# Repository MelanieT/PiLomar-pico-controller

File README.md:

# Pilomar Pico firmware

## Firmware for driving two standard stepper drivers

You can use the board files in hardware/ to have the board fabbed, or you can use a stock pico and wire up the stepper drivers according to the schematic.

The pico will appear as a USB network device and two serial ports, the first of which is the console, which is also available on a JST-SM connector on the board.

It serves a REST API as described in the PilomarAPI.yaml file, which is maintained in the jPiLomar project.

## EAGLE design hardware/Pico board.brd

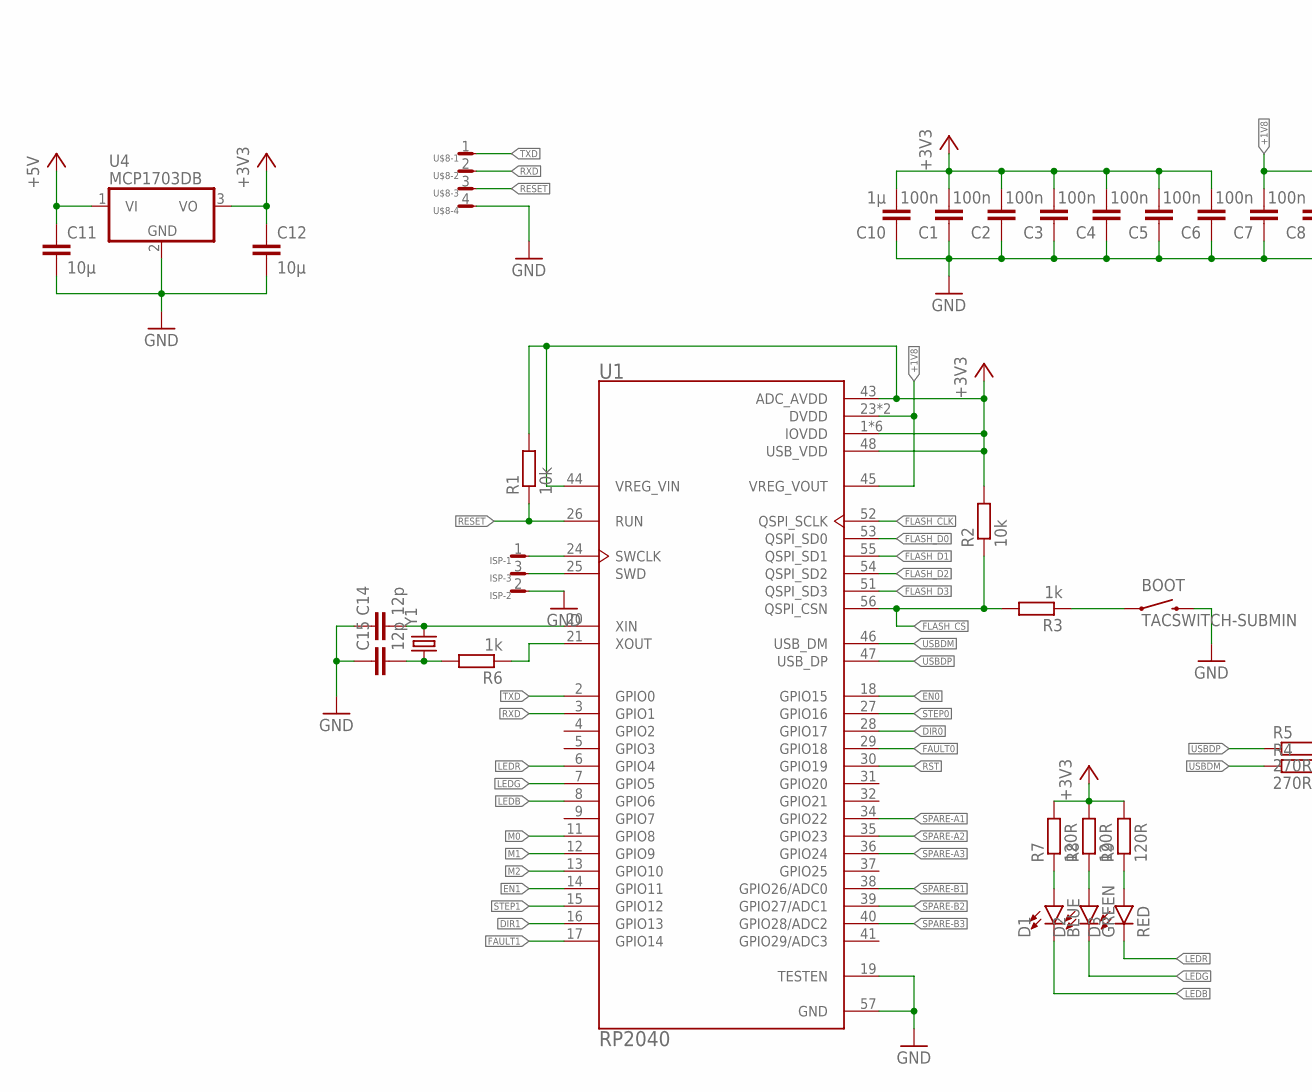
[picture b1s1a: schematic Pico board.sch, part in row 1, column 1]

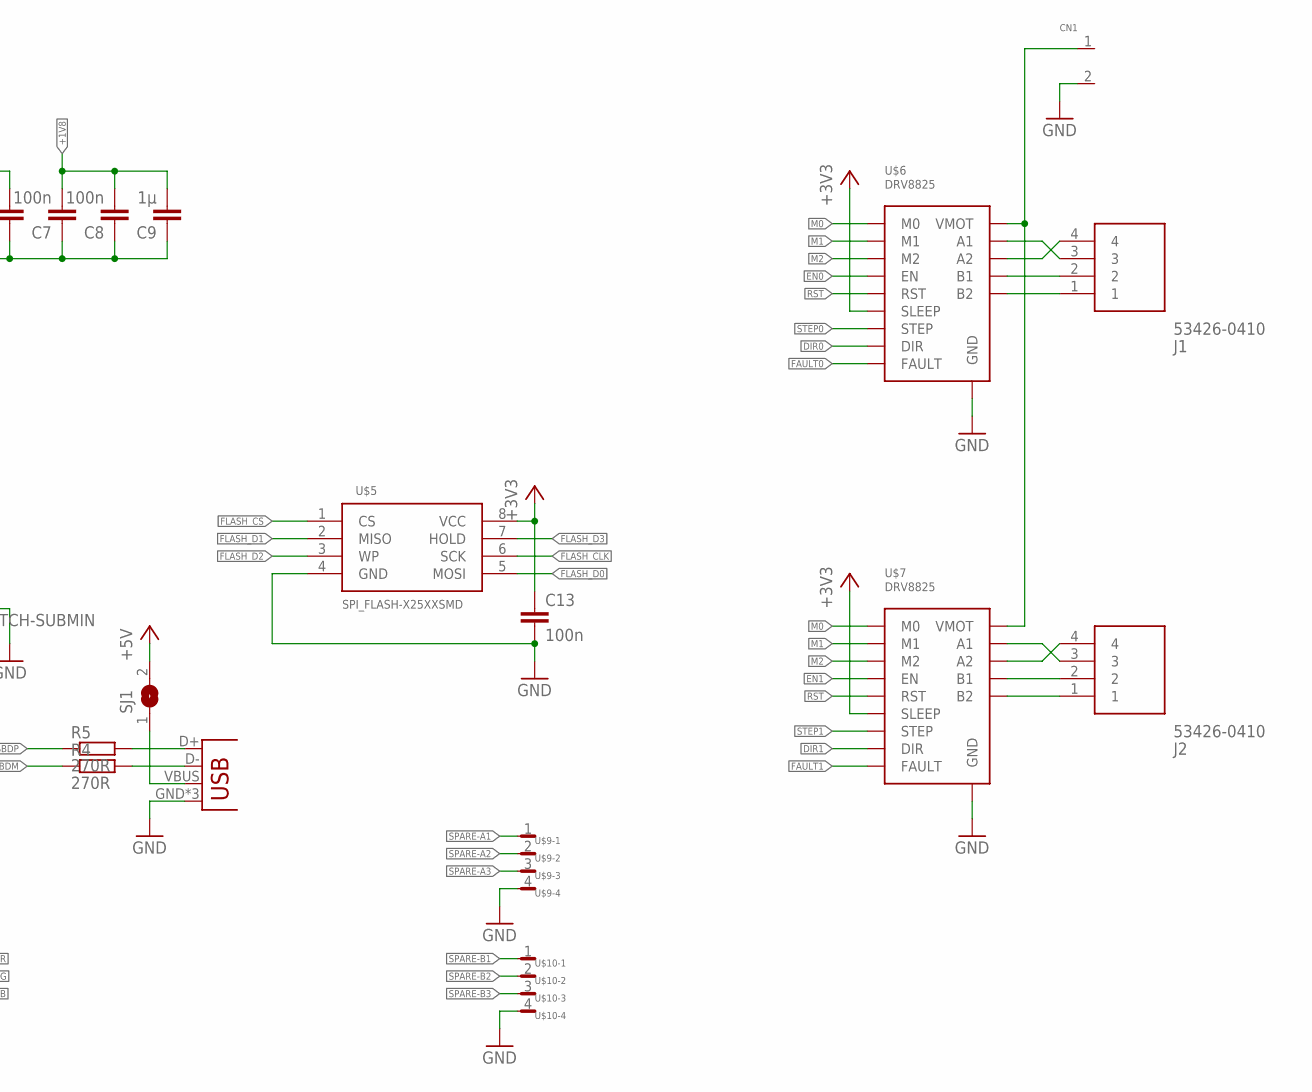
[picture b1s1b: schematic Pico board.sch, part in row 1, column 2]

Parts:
BOOT: TACSWITCH-SUBMIN; TACSWITCH_SUBMIN
C1, C2, C3, C4, C5, C6, C7, C8, C13: 100n; C0402K
C9, C10: 1µ; C0603K
C11, C12: 10µ; C1206K
C14, C15: 12p; C0402K
CN1: 2PIN_SCREW_TRM; CONN2P
D1: BLUE; LED-0603
D2: GREEN; LED-0603
D3: RED; LED-0603
ISP: SM03B-SRSS-TB
J1, J2: 53426-0410; SHDRRA4W55P0X250_1X4_1240X1150
JP1: USB-MICROB
R1, R2: 10k; R0402
R3, R6: 1k; R0402
R4, R5: 270R; R0402
R7, R8, R9: 120R; R0402
SJ1: SJ
U1: RP2040; QFN40P700X700X90-57N
U4: MCP1703DB; SOT223
U$5: SPI_FLASH-X25XXSMD; SO08
U$6, U$7: DRV8825; POLOLU
U$8, U$9, U$10: SM04B-SRSS-TB
Y1: CRYSTAL5X3; CRYSTAL-SMD-5X3

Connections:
+1V8: C7.2, C8.2, C9.2, U1.23 (DVDD), U1.45 (VREG_VOUT), U1.50 (DVDD)
+3V3: C1.2, C2.2, C3.2, C4.2, C5.2, C6.2, C10.2, C12.1, C13.1, R1.2, R2.2, R7.2, R8.2, R9.2, U1.1 (IOVDD), U1.10 (IOVDD), U1.22 (IOVDD), U1.33 (IOVDD), U1.42 (IOVDD), U1.43 (ADC_AVDD), U1.44 (VREG_VIN), U1.48 (USB_VDD), U1.49 (IOVDD), U4.3 (VO), U$5.8 (VCC), U$6.SLEEP, U$7.SLEEP
+5V: C11.1, SJ1.2, U4.1 (VI)
DIR0: U1.28 (GPIO17), U$6.DIR
DIR1: U1.16 (GPIO13), U$7.DIR
EN0: U1.18 (GPIO15), U$6.ENABLE (EN)
EN1: U1.14 (GPIO11), U$7.ENABLE (EN)
FAULT0: U1.29 (GPIO18), U$6.FAULT
FAULT1: U1.17 (GPIO14), U$7.FAULT
FLASH_CLK: U1.52 (QSPI_SCLK), U$5.6 (SCK)
FLASH_CS: R2.1, R3.2, U1.56 (QSPI_CSN), U$5.1 (CS)
FLASH_D0: U1.53 (QSPI_SD0), U$5.5 (MOSI)
FLASH_D1: U1.55 (QSPI_SD1), U$5.2 (MISO)
FLASH_D2: U1.54 (QSPI_SD2), U$5.3 (WP)
FLASH_D3: U1.51 (QSPI_SD3), U$5.7 (HOLD)
GND: BOOT.-2 (2), C1.1, C2.1, C3.1, C4.1, C5.1, C6.1, C7.1, C8.1, C9.1, C10.1, C11.2, C12.2, C13.2, C14.1, C15.1, CN1.2, ISP.2, JP1.GND, JP1.MT1 (GND), JP1.MT2 (GND), U1.19 (TESTEN), U1.57 (GND), U4.2 (GND), U$5.4 (GND), U$6.GND@1 (GND), U$6.GND@2 (GND), U$7.GND@1 (GND), U$7.GND@2 (GND), U$8.4, U$9.4, U$10.4
LEDB: D1.C, U1.8 (GPIO6)
LEDG: D2.C, U1.7 (GPIO5)
LEDR: D3.C, U1.6 (GPIO4)
M0: U1.11 (GPIO8), U$6.M0, U$7.M0
M1: U1.12 (GPIO9), U$6.M1, U$7.M1
M2: U1.13 (GPIO10), U$6.M2, U$7.M2
unnamed: J1.3, U$6.A1
unnamed: JP1.D+, R5.2
unnamed: JP1.D-, R4.2
unnamed: J1.4, U$6.A2
unnamed: BOOT.-1 (1), R3.1
unnamed: J2.2, U$7.B1
unnamed: J2.1, U$7.B2
unnamed: J2.3, U$7.A1
unnamed: J2.4, U$7.A2
unnamed: JP1.VBUS, SJ1.1
unnamed: ISP.1, U1.24 (SWCLK)
unnamed: ISP.3, U1.25 (SWD)
unnamed: C15.2, R6.2, Y1.1
unnamed: R6.1, U1.21 (XOUT)
unnamed: C14.2, U1.20 (XIN), Y1.3 (2)
unnamed: J1.2, U$6.B1
unnamed: J1.1, U$6.B2
unnamed: D1.A, R7.1
unnamed: D2.A, R8.1
unnamed: CN1.1, U$6.VMOT, U$7.VMOT
unnamed: D3.A, R9.1
RESET: R1.1, U1.26 (RUN), U$8.3
RST: U1.30 (GPIO19), U$6.RESET (RST), U$7.RESET (RST)
RXD: U1.3 (GPIO1), U$8.2
SPARE-A1: U1.34 (GPIO22), U$9.1
SPARE-A2: U1.35 (GPIO23), U$9.2
SPARE-A3: U1.36 (GPIO24), U$9.3
SPARE-B1: U1.38 (GPIO26/ADC0), U$10.1
SPARE-B2: U1.39 (GPIO27/ADC1), U$10.2
SPARE-B3: U1.40 (GPIO28/ADC2), U$10.3
STEP0: U1.27 (GPIO16), U$6.STEP
STEP1: U1.15 (GPIO12), U$7.STEP
TXD: U1.2 (GPIO0), U$8.1
USBDM: R4.1, U1.46 (USB_DM)
USBDP: R5.1, U1.47 (USB_DP)

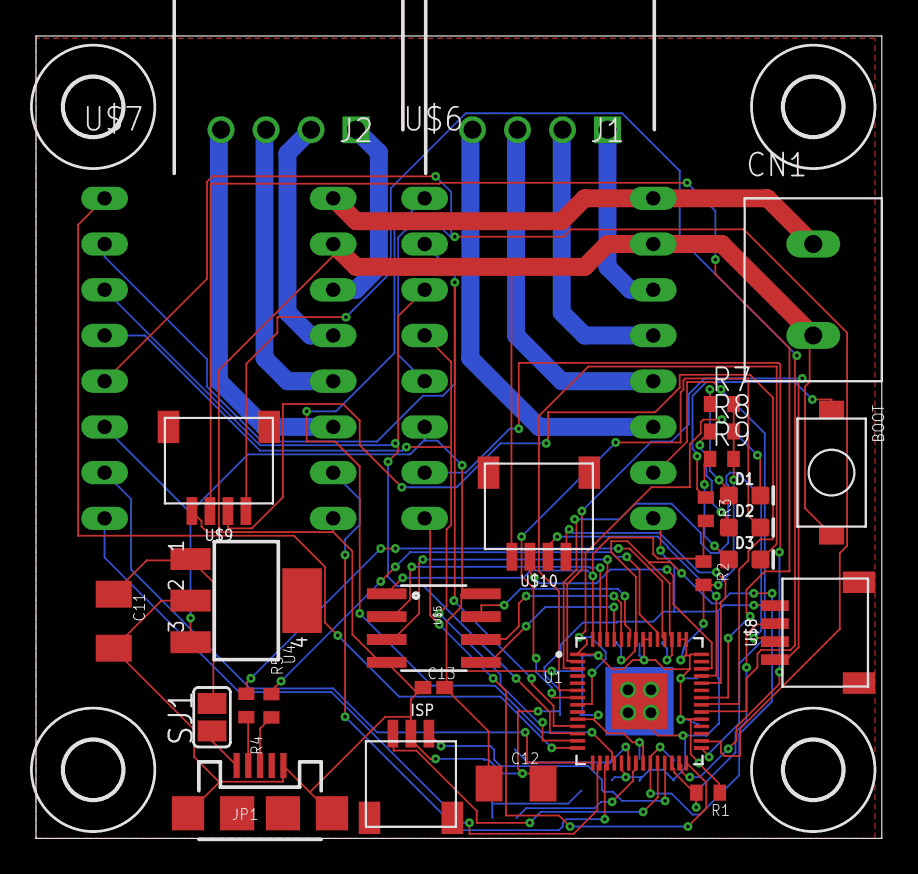
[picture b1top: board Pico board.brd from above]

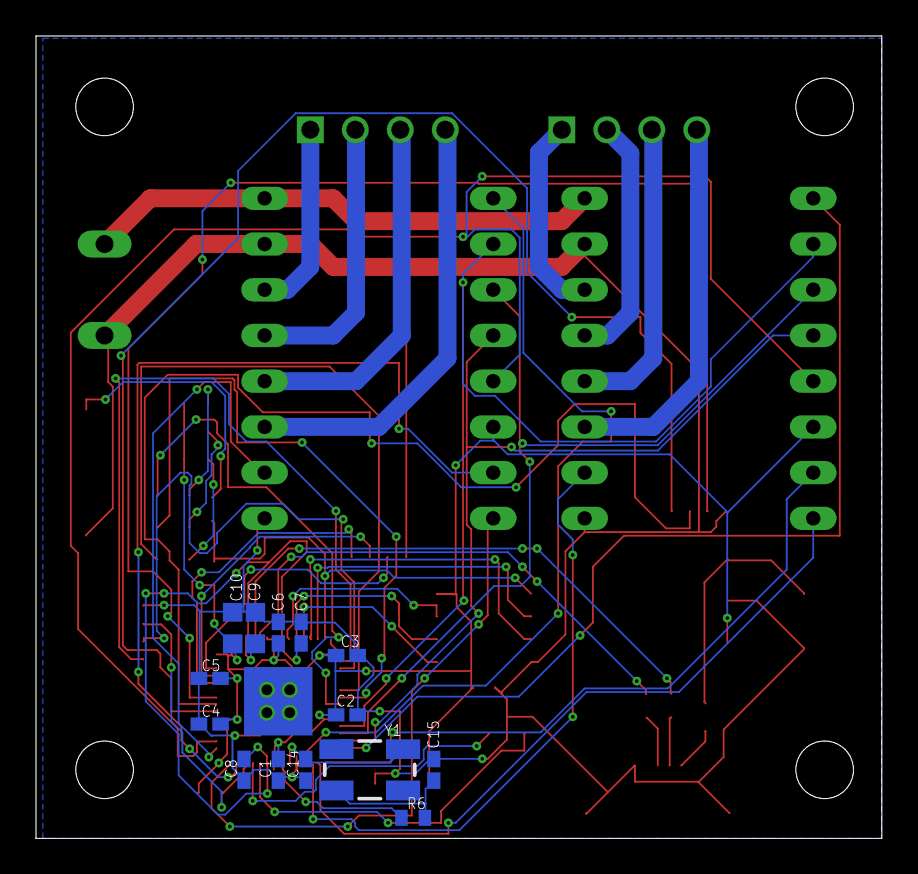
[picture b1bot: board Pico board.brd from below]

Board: 2 copper layers, 47.0 x 44.6 mm, 47 parts (14 on the bottom side), 57 nets.

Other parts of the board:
U$1, U$2, U$3, U$4: 3,2

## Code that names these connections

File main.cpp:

// SPDX-FileCopyrightText: 2024 Melanie Thielker & Leonie Gaertner
// SPDX-License-Identifier: BSD-3-Clause

#include <cstdio>
#include <pico/time.h>
#include <hardware/gpio.h>
#include <vector>
#include <pico/stdlib.h>
#include <hardware/flash.h>
#include "pico/stdio.h"
#include "Motor.h"
#include "tusb.h"
#include "tusb_lwip_glue.h"
#include "webserver/WebServer-lwip.h"
#include "webserver/ApiServer.h"
#include "UrlMapper.h"
#include "nlohmann/json.hpp"

#define MODE_DOOR 0
#define MODE_CAMERA 1
#define MODE MODE_CAMERA

#define LED_BLUE  4
#define LED_GREEN 5
#define LED_RED   6
#define STEP_M0   8
#define STEP_M1   9
#define STEP_M2   10
#define RST       19
#define EN0       15
#define STEP0     16
#define DIR0      17
#define VCC0      18
#define EN1       11
#define STEP1     12
#define DIR1      13
#define VCC1      14

#define SPARE_A1  22
#define SPARE_A2  23
#define SPARE_A3  24

#define SPARE_B1  26
#define SPARE_B2  27
#define SPARE_B3  28

#define AZIMUTH_MAX_SPEED 8000
#define AZIMUTH_STEPS_PER_REVOLUTION 384000
#define AZIMUTH_MAX_STEPS 384000 //373334

#define ELEVATION_MAX_SPEED 8000
#define ELEVATION_STEPS_PER_REVOLUTION 384000
#define ELEVATION_MAX_STEPS 120000
#define ELEVATION_ZERO_POINT 22500

#define DOOR_MAX_STEPS 2125
#define DOOR_MAX_SPEED 400

using namespace nlohmann;

uint8_t macaddr[6];

uint8_t tud_network_mac_address[6];

Motor *stepper0;
Motor *stepper1;

WebServerLwip webserver;

class PilomarApi
{
public:
    static void Init()
    {
        UrlMapper::AddMapping("GET", "/info", &info);
        UrlMapper::AddMapping("POST", "/move", &move);
    }
private:
#if MODE == MODE_DOOR
    static void move(const HttpRequest& request, HttpResponse& response)
    {
        auto payload = json::parse(request.body(), nullptr, false);
        if (payload.is_discarded())
        {
            response.setStatusCode(HttpStatus::Code::BadRequest);
            return;
        }

        if (stepper0->isRunning() || stepper1->isRunning())
        {
            response.setStatusCode(HttpStatus::Code::PreconditionFailed);
            return;
        }

        auto mode = payload.value<std::string>("mode", "move");

        if (mode == "move")
        {
            int position = payload.value("position", -1);
            int speed = payload.value("speed", DOOR_MAX_SPEED);

            if (position < 0 || position > DOOR_MAX_STEPS || speed < 10 || speed > DOOR_MAX_SPEED)
            {
                response.setStatusCode(HttpStatus::Code::BadRequest);
                return;
            }
            stepper0->runToTarget(speed, position);
            stepper1->runToTarget(speed, position);
        }
        else if (mode == "learn")
        {
            stepper0->setCurrentPosition(DOOR_MAX_STEPS);
            stepper1->setCurrentPosition(DOOR_MAX_STEPS);
            stepper0->runToTarget(DOOR_MAX_SPEED, 0);
            stepper1->runToTarget(DOOR_MAX_SPEED, 0);
        }
        else
        {
            response.setStatusCode(HttpStatus::Code::BadRequest);
            return;
        }

        response.setBody(
                json{
                    {"result", "ok"}
                }.dump()
            );
    }
#elif MODE == MODE_CAMERA
#pragma clang diagnostic push
#pragma ide diagnostic ignored "bugprone-branch-clone"
    static void move(const HttpRequest& request, HttpResponse& response)
    {
        auto payload = json::parse(request.body(), nullptr, false);
        if (payload.is_discarded())
        {
            response.setStatusCode(HttpStatus::Code::BadRequest);
            return;
        }

        auto motor = payload.value<std::string>("motor", "");
        Motor *m = nullptr;
        if (motor == "azimuth")
            m = stepper1;
        else if (motor == "elevation")
            m = stepper0;

        if (!m)
        {
            response.setStatusCode(HttpStatus::Code::BadRequest);
            return;
        }

//        if (m->isRunning())
//        {
//            response.setStatusCode(HttpStatus::Code::PreconditionFailed);
//            return;
//        }

        int maxSpeed = motor == "elevation" ? ELEVATION_MAX_SPEED : AZIMUTH_MAX_SPEED;
        int maxSteps = motor == "elevation" ? ELEVATION_MAX_STEPS : AZIMUTH_MAX_STEPS;

        int position = payload.value("position", -1);
        auto speed = payload.value<double>("speed", (double)maxSpeed);

        if (position < 0 || position > maxSteps || speed < 0.0001 || speed > maxSpeed)
        {
            response.setStatusCode(HttpStatus::Code::BadRequest);
            return;
        }

        m->runToTarget(speed, position);

        response.setBody(
            json{
                {"result", "ok"}
            }.dump()
        );
    }
#pragma clang diagnostic pop
#endif
    static void info(const HttpRequest& request, HttpResponse& response)
    {
        response.setBody(
            json{
#if MODE == MODE_DOOR
                {"type", "door"},
                {"max_steps", DOOR_MAX_STEPS},
                {"max_speed", DOOR_MAX_SPEED},
                {"position_left", stepper0->getCurrentPosition()},
                {"position_right", stepper1->getCurrentPosition()},
                {"closed_position", 0},
                {"open_position", DOOR_MAX_STEPS}
#elif MODE == MODE_CAMERA
                {"type", "camera"},
                {"azimuth", stepper1->getCurrentPosition()},
                {"elevation", stepper0->getCurrentPosition()},
                {"max_elevation", ELEVATION_MAX_STEPS},
                {"max_azimuth", AZIMUTH_MAX_STEPS},
                {"max_speed_azimuth", AZIMUTH_MAX_SPEED},
                {"max_speed_elevation", ELEVATION_MAX_SPEED}
#endif
            }.dump()
        );
    }
};

void usbd_serial_init(void)
{
    uint8_t id[8];

    flash_get_unique_id(id);

    tud_network_mac_address[0] = 0xb8;
    tud_network_mac_address[1] = 0x27;
    tud_network_mac_address[2] = 0xeb;
    tud_network_mac_address[3] = id[5];
    tud_network_mac_address[4] = id[6];
    tud_network_mac_address[5] = id[7];
}

#pragma clang diagnostic push
#pragma ide diagnostic ignored "EndlessLoop"
int main()
{
    usbd_serial_init();
    tusb_init();
    stdio_init_all();

    init_lwip();

    wait_for_netif_is_up();

    dhcpd_init();

    webserver.Init();
    PilomarApi::Init();

    std::vector<uint> gpios_out = {4, 5, 6, 8, 9, 10, 11, 12, 13, 14, 15, 16, 17, 18, 19};
    std::vector<uint> gpios_in = {};

    for (auto p: gpios_out)
    {
        gpio_init(p);
        gpio_set_dir(p, true);
        gpio_put(p, true);
    }

    for (auto p: gpios_in)
    {
        gpio_init(p);
        gpio_set_dir(p, false);
    }

    gpio_put(LED_GREEN, false);

    // Reset stepper drivers
    gpio_put(RST, false);
    sleep_ms(10);
    gpio_put(RST, true);

    // Set step ouputs to low
    gpio_put(STEP0, false);
    gpio_put(STEP1, false);

#if MODE == MODE_CAMERA
    gpio_put(STEP_M0, true);
    gpio_put(STEP_M1, true);
    gpio_put(STEP_M2, false);
#elif MODE == MODE_DOOR
    gpio_put(STEP_M0, false);
    gpio_put(STEP_M1, false);
    gpio_put(STEP_M2, false);
#endif


    gpio_put(DIR0, true); // false is up
    gpio_put(DIR1, true); // false is clockwise

//    Motor stepper((Pins){STEP0, DIR0, EN0, SPARE_B3, false, true}, ELEVATION_STEPS_PER_REVOLUTION, ELEVATION_MAX_STEPS);
//    Motor stepper0((Pins){STEP0, DIR0, EN0, -1, false, false}, AZIMUTH_STEPS_PER_REVOLUTION, AZIMUTH_MAX_STEPS);
//    Motor stepper1((Pins){STEP1, DIR1, EN1, -1, false, false}, AZIMUTH_STEPS_PER_REVOLUTION, AZIMUTH_MAX_STEPS);
//

#if MODE == MODE_DOOR
    stepper0 = new Motor((Pins){STEP0, DIR0, EN0}, (Options){.autoPowerOff = true, .reverse = true, .microsteps = 1}, DOOR_MAX_STEPS, DOOR_MAX_STEPS);
    stepper1 = new Motor((Pins){STEP1, DIR1, EN1}, (Options){.autoPowerOff = true, .reverse = true, .microsteps = 1}, DOOR_MAX_STEPS, DOOR_MAX_STEPS);
#elif MODE == MODE_CAMERA
    stepper0 = new Motor((Pins){STEP0, DIR0, EN0}, (Options){.reverse = true, .endstop = SPARE_B3, .dirToEndstop = false}, ELEVATION_STEPS_PER_REVOLUTION, ELEVATION_MAX_STEPS);
    stepper1 = new Motor((Pins){STEP1, DIR1, EN1}, (Options){}, AZIMUTH_STEPS_PER_REVOLUTION, AZIMUTH_MAX_STEPS);
#endif

    uint64_t ticks = 0;

    while (true)
    {
//        if (tud_cdc_n_available(1))
//        {
//            char c = tud_cdc_n_read_char(1);
//            tud_cdc_n_write_char(1, c);
//            tud_cdc_n_write_flush(1);
//        }
        ++ticks;

        if (!(ticks % 5000))
        {
//            printf("Blink\n");
            gpio_put(LED_RED, !gpio_get_out_level(LED_RED));
        }

        tud_task();
        service_traffic();
        webserver.ProcessMessages(ApiServer::RequestHandler);

        sleep_us(100);
    }
}
#pragma clang diagnostic pop

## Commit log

2024-03-05 Start adding license and copyrights
2024-03-05 Remove unneeded files
2024-03-05 Add license headers
2024-03-05 Fill in README
2024-03-05 Restore accidentally deleted files
2024-03-06 Tolerate double slashes in URL. Add new fields to camera info
2024-03-07 Assemble received packets until one full http message is received
2024-03-17 Remove openapi spec, it was outdated and lives somewhere else now.
2024-03-17 Add hardware files
2024-03-17 Adjust README
2024-03-25 Switch to our own registered USB vid/pid

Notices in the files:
parts and their libraries:
SparkFun-FreqCtrl: Licensing: CC v3.0 Share-Alike You are welcome to use this library for commercial purposes.
SparkFun-LED: Licensing: Creative Commons ShareAlike 4.0 International - https://creativecommons.org/licenses/by-sa/4.0
